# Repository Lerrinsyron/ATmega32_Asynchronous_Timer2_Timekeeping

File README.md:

ATmega32 Asynchronous Timer2 Timekeeping

CT 321 — Group 13 

Low-power real-time clock using ATmega32 Timer2 in asynchronous mode, driven by a 32.768 kHz watch crystal on TOSC1/TOSC2. The CPU sleeps between timer events; Timer2 keeps running and wakes the CPU exactly once per second.

Build
```bash
cd firmware

# Real hardware
avr-gcc -mmcu=atmega32 -DF_CPU=8000000UL -Os -I/usr/avr/include \
  -o hex/firmware.elf src/main.c
avr-objcopy -O ihex -R .eeprom hex/firmware.elf hex/firmware.hex

# SimulIDE
avr-gcc -mmcu=atmega32 -DF_CPU=8000000UL -DSIMULIDE_MODE -Os -I/usr/avr/include \
  -o hex/firmware_simulide.elf src/main.c
avr-objcopy -O ihex -R .eeprom hex/firmware_simulide.elf hex/firmware_simulide.hex
```

If `/usr/avr/include` doesn't exist on your machine, run `find /usr -name "io.h" | grep avr` to find your avr-libc path.

SimulIDE

Load hex/firmware_simulide.hex into the ATmega32. Set Freq to `8000000` and Serial Monitor baud to `9600`.

> ⚠️ Known limitation: SimulIDE cannot model the external 32.768 kHz crystal on TOSC1/TOSC2. The SIMULIDE_MODE   build uses an internal-clock CTC fallback to produce the same 1-second tick. The KiCad design remains correct for real hardware.

Common Issues

Garbage output on serial monitor baud rate mismatch. Confirm SimulIDE Serial Monitor is set to 9600, not 4800.

"SLEEP instruction not fully implemented" warning expected. SimulIDE does not model power-save sleep. Ignore it; everything else works correctly.

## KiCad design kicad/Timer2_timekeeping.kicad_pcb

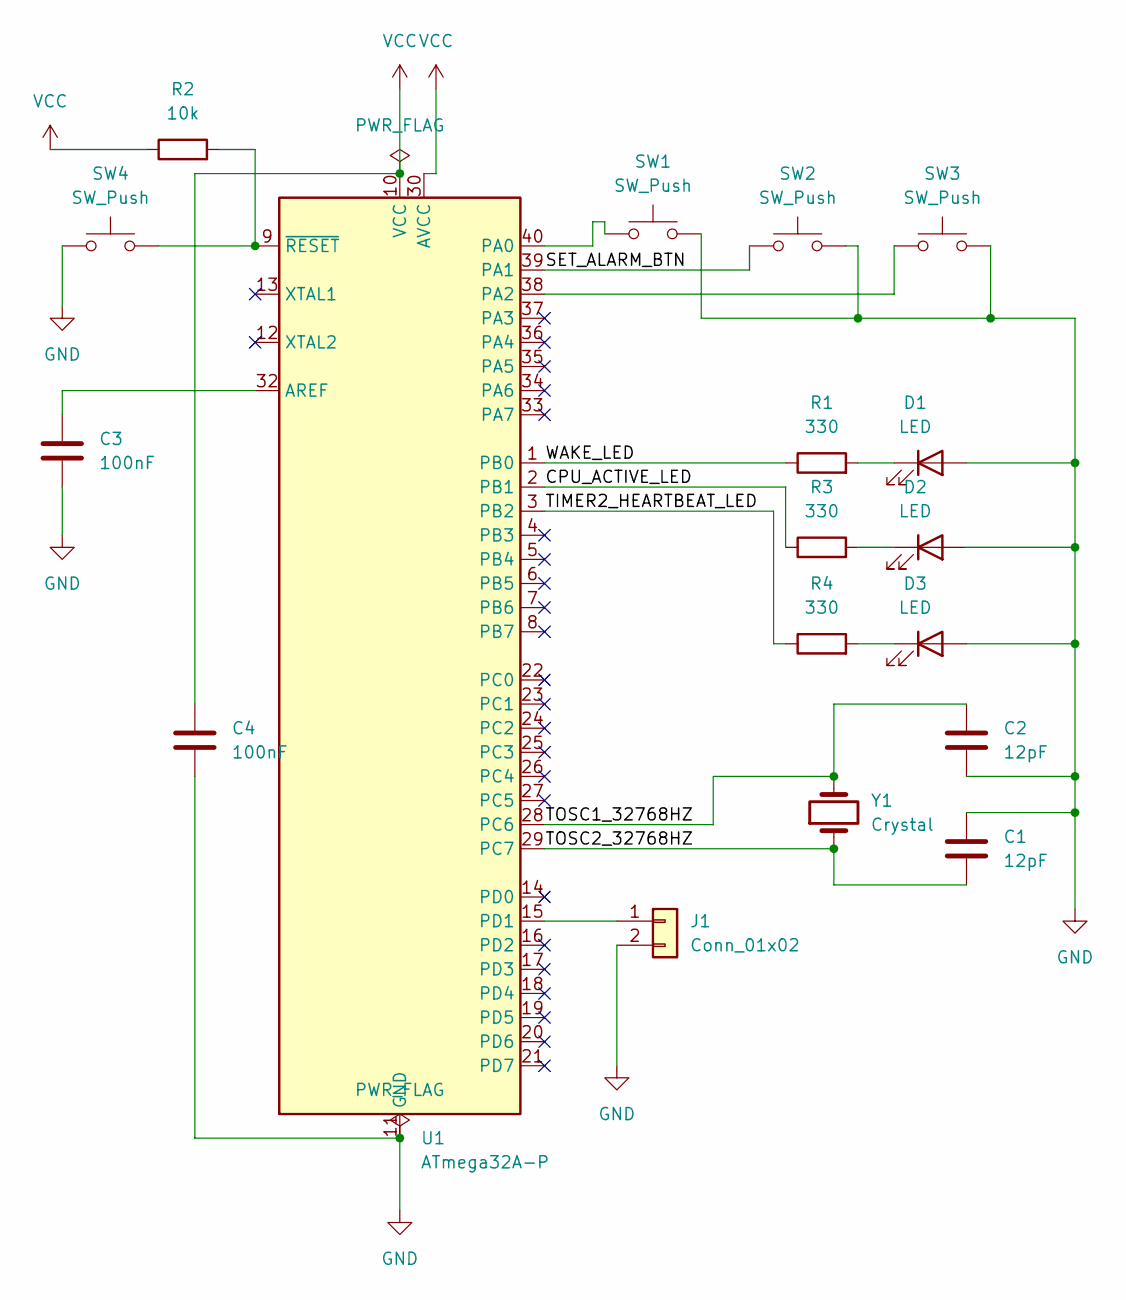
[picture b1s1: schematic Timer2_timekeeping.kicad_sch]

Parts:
C1, C2: 12pF; C_Disc_D5.0mm_W2.5mm_P5.00mm
C3, C4: 100nF; C_Disc_D5.0mm_W2.5mm_P5.00mm
D1, D2, D3: LED; LED_D5.0mm
J1: Conn_01x02; PinHeader_1x02_P2.54mm_Vertical
R1, R3, R4: 330; R_Axial_DIN0207_L6.3mm_D2.5mm_P7.62mm_Horizontal
R2: 10k; R_Axial_DIN0207_L6.3mm_D2.5mm_P7.62mm_Horizontal
SW1, SW2, SW3, SW4: SW_Push; SW_PUSH_6mm
U1: ATmega32A-P; DIP-40_W15.24mm
Y1: Crystal; Crystal_HC49-4H_Vertical

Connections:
/CPU_ACTIVE_LED: R3.1, U1.2 (PB1)
/SET_ALARM_BTN: SW2.1, U1.39 (PA1)
/TIMER2_HEARTBEAT_LED: R4.1, U1.3 (PB2)
/TOSC1_32768HZ: C2.1, U1.28 (PC6), Y1.2
/TOSC2_32768HZ: C1.2, U1.29 (PC7), Y1.1
/WAKE_LED: R1.1, U1.1 (PB0)
GND: C1.1, C2.2, C3.2, C4.1, D1.2 (A), D2.2 (A), D3.2 (A), J1.2, SW1.2, SW2.2, SW3.2, SW4.1, U1.11 (GND), U1.31 (GND)
unnamed: D1.1 (K), R1.2
unnamed: D2.1 (K), R3.2
unnamed: D3.1 (K), R4.2
unnamed: J1.1, U1.15 (PD1)
unnamed: C3.1, U1.32 (AREF)
unnamed: SW1.1, U1.40 (PA0)
unnamed: SW3.1, U1.38 (PA2)
unnamed: R2.2, SW4.2, U1.9 (~RESET)
VCC: C4.2, R2.1, U1.10 (VCC), U1.30 (AVCC)

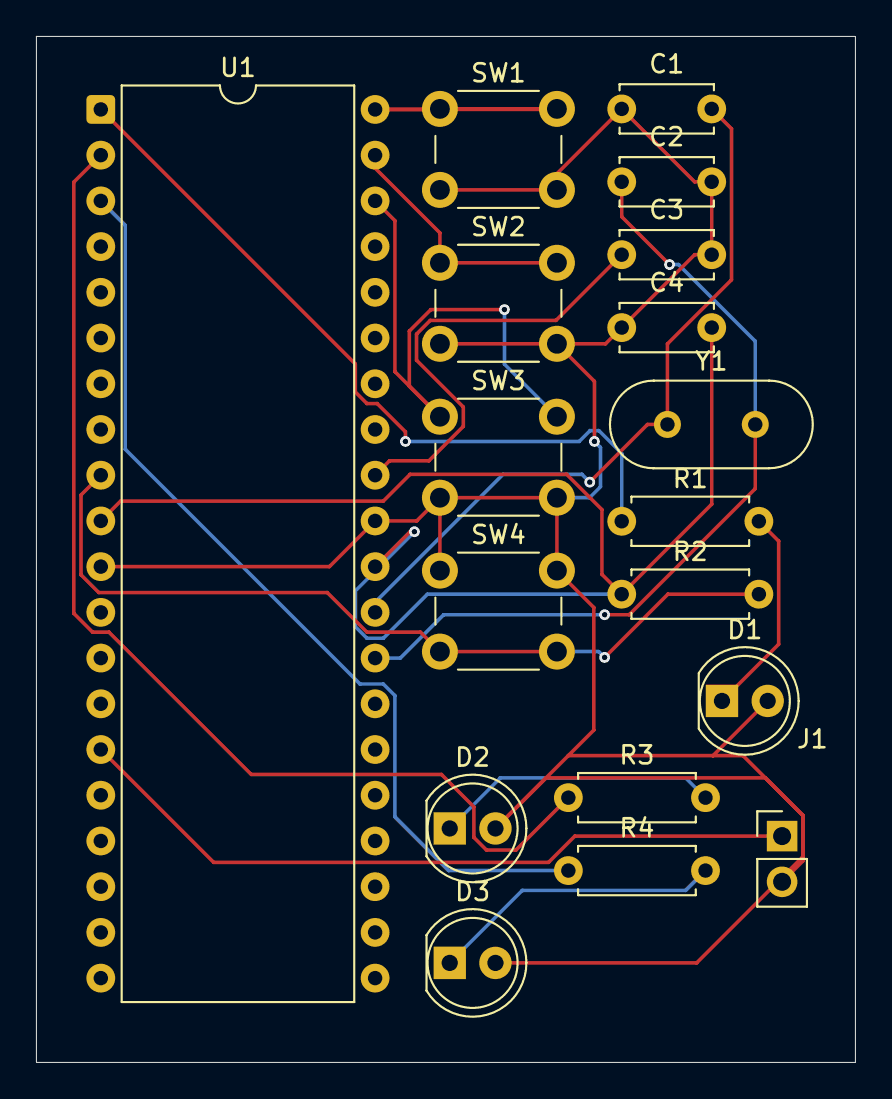
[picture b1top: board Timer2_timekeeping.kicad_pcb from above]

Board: 2 copper layers, 45.5 x 57.0 mm, 18 parts (0 on the bottom side), 16 nets.

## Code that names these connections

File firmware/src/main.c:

#define F_CPU 8000000UL

#include <avr/interrupt.h>
#include <avr/io.h>
#include <avr/sleep.h>
#include <stdbool.h>
#include <stdio.h>
#include <string.h>
#include <util/delay.h>

// configs
#define WAKE_LED_PIN PB0
#define BUZZER_PIN PB1
#define BTN_RESET PA0
#define BTN_SET_ALARM PA1
#define BTN_INCREMENT PA2

#define ALARM_BUZZ_DURATION 3

#define WAKEUP_INTERVAL 10

#define BAUD 9600
#define UBRR_VALUE ((F_CPU / (16UL * BAUD)) - 1) // = 51 at 8 MHz 

volatile uint8_t g_seconds = 0;
volatile uint8_t g_minutes = 0;
volatile uint8_t g_hours = 0;

volatile uint8_t g_alarm_seconds = 0;
volatile uint8_t g_alarm_minutes = 0;
volatile uint8_t g_alarm_hours = 0;

volatile bool g_time_updated = false; 
volatile bool g_alarm_ringing = false;
volatile uint8_t g_buzz_countdown = 0; 

#ifdef SIMULIDE_MODE
volatile uint8_t g_tick_count = 0;
#define TICKS_PER_SECOND 100 
#endif

typedef enum
{
  MODE_CLOCK,       
  MODE_SET_ALARM_H, 
  MODE_SET_ALARM_M, 
  MODE_SET_ALARM_S  
} AppMode;

volatile AppMode g_mode = MODE_CLOCK;


static void usart_init(void)
{
  UBRRH = (uint8_t)(UBRR_VALUE >> 8);
  UBRRL = (uint8_t)(UBRR_VALUE);
  UCSRB = (1 << TXEN);                                
  UCSRC = (1 << URSEL) | (1 << UCSZ1) | (1 << UCSZ0); 
}

static void usart_putchar(char c)
{
  while (!(UCSRA & (1 << UDRE)))
    ;
  UDR = c;
}

static void usart_print(const char *str)
{
  while (*str)
    usart_putchar(*str++);
}

static void usart_print_time(uint8_t h, uint8_t m, uint8_t s,
                             const char *label)
{
  char buf[32];
  snprintf(buf, sizeof(buf), "%s %02u:%02u:%02u\r\n", label, h, m, s);
  usart_print(buf);
}

static void gpio_init(void)
{
  DDRB |= (1 << WAKE_LED_PIN) | (1 << BUZZER_PIN) | (1 << PB2) | (1 << PB3);
  PORTB &= ~((1 << WAKE_LED_PIN) | (1 << BUZZER_PIN) | (1 << PB2) | (1 << PB3)); 

  DDRA &= ~((1 << BTN_RESET) | (1 << BTN_SET_ALARM) | (1 << BTN_INCREMENT));
  PORTA |= (1 << BTN_RESET) | (1 << BTN_SET_ALARM) | (1 << BTN_INCREMENT);
}

static void timer2_init(void)
{
#ifndef SIMULIDE_MODE
  //Async clock source
  ASSR |= (1 << AS2);

  TCNT2 = 0;

  TCCR2 = (1 << CS22) | (1 << CS20);

  while (ASSR & ((1 << TCN2UB) | (1 << OCR2UB) | (1 << TCR2UB)))
    ;
  TIMSK |= (1 << TOIE2);

#else
  TCCR2 = (1 << WGM21)                               
          | (1 << CS22) | (1 << CS21) | (1 << CS20); 
  OCR2 = 77;                                         
  TIMSK |= (1 << OCIE2);                            
#endif
}

#ifndef SIMULIDE_MODE

ISR(TIMER2_OVF_vect)
{
  g_seconds++;
  if (g_seconds >= 60)
  {
    g_seconds = 0;
    g_minutes++;
  }
  if (g_minutes >= 60)
  {
    g_minutes = 0;
    g_hours++;
  }
  if (g_hours >= 24)
  {
    g_hours = 0;
  }

  if (g_seconds % WAKEUP_INTERVAL == 0)
    PORTB ^= (1 << WAKE_LED_PIN);

  if (!g_alarm_ringing && g_hours == g_alarm_hours &&
      g_minutes == g_alarm_minutes && g_seconds == g_alarm_seconds)
  {
    g_alarm_ringing = true;
    g_buzz_countdown = ALARM_BUZZ_DURATION;
    PORTB |= (1 << BUZZER_PIN);
  }


  if (g_alarm_ringing)
  {
    if (g_buzz_countdown > 0)
    {
      g_buzz_countdown--;
    }
    else
    {
      g_alarm_ringing = false;
      PORTB &= ~(1 << BUZZER_PIN);
    }
  }

  PORTB ^= (1 << PB3);
  g_time_updated = true;
}

#else 
ISR(TIMER2_COMP_vect)
{
  g_tick_count++;
  if (g_tick_count < TICKS_PER_SECOND)
    return; 
  g_tick_count = 0;

  
  g_seconds++;
  if (g_seconds >= 60)
  {
    g_seconds = 0;
    g_minutes++;
  }
  if (g_minutes >= 60)
  {
    g_minutes = 0;
    g_hours++;
  }
  if (g_hours >= 24)
  {
    g_hours = 0;
  }

  if (g_seconds % WAKEUP_INTERVAL == 0)
    PORTB ^= (1 << WAKE_LED_PIN);

  if (!g_alarm_ringing && g_hours == g_alarm_hours &&
      g_minutes == g_alarm_minutes && g_seconds == g_alarm_seconds)
  {
    g_alarm_ringing = true;
    g_buzz_countdown = ALARM_BUZZ_DURATION;
    PORTB |= (1 << BUZZER_PIN);
  }

  if (g_alarm_ringing)
  {
    if (g_buzz_countdown > 0)
    {
      g_buzz_countdown--;
    }
    else
    {
      g_alarm_ringing = false;
      PORTB &= ~(1 << BUZZER_PIN);
    }
  }

  PORTB ^= (1 << PB3);
  g_time_updated = true;
}

#endif 

static bool button_pressed(uint8_t pin)
{
  if (!(PINA & (1 << pin)))
  {                           
    _delay_ms(20);            
    if (!(PINA & (1 << pin))) 
      return true;
  }
  return false;
}

static void handle_buttons(void)
{
  if (button_pressed(BTN_RESET))
  {
    cli(); 
    g_seconds = 0;
    g_minutes = 0;
    g_hours = 0;
    g_alarm_ringing = false;
    g_buzz_countdown = 0;
    PORTB &= ~((1 << WAKE_LED_PIN) | (1 << BUZZER_PIN));
    g_mode = MODE_CLOCK;
    sei();
    usart_print("TIME RESET TO 00:00:00\r\n");
    while (!(PINA & (1 << BTN_RESET)))
      ;
    _delay_ms(20);
    return;
  }

  if (button_pressed(BTN_SET_ALARM))
  {
    switch (g_mode)
    {
    case MODE_CLOCK:
      g_mode = MODE_SET_ALARM_H;
      break;
    case MODE_SET_ALARM_H:
      g_mode = MODE_SET_ALARM_M;
      break;
    case MODE_SET_ALARM_M:
      g_mode = MODE_SET_ALARM_S;
      break;
    case MODE_SET_ALARM_S:
      g_mode = MODE_CLOCK;
      break;
    }
    while (!(PINA & (1 << BTN_SET_ALARM)))
      ;
    _delay_ms(20);
  }

  if (button_pressed(BTN_INCREMENT))
  {
    switch (g_mode)
    {
    case MODE_CLOCK:
      break; 
    case MODE_SET_ALARM_H:
      g_alarm_hours = (g_alarm_hours + 1) % 24;
      break;
    case MODE_SET_ALARM_M:
      g_alarm_minutes = (g_alarm_minutes + 1) % 60;
      break;
    case MODE_SET_ALARM_S:
      g_alarm_seconds = (g_alarm_seconds + 1) % 60;
      break;
    }
    while (!(PINA & (1 << BTN_INCREMENT)))
      ;
    _delay_ms(20);
  }
}

static void update_display(void)
{
  cli();
  uint8_t h = g_hours, m = g_minutes, s = g_seconds;
  uint8_t ah = g_alarm_hours, am = g_alarm_minutes, as_ = g_alarm_seconds;
  AppMode mode = g_mode;
  g_time_updated = false;
  sei();

  usart_print_time(h, m, s, "TIME: ");

  usart_print_time(ah, am, as_, "ALRM: ");

  switch (mode)
  {
  case MODE_CLOCK:
    usart_print("MODE: LOW POWER\r\n");
    break;
  case MODE_SET_ALARM_H:
    usart_print("MODE: SET ALARM HH\r\n");
    break;
  case MODE_SET_ALARM_M:
    usart_print("MODE: SET ALARM MM\r\n");
    break;
  case MODE_SET_ALARM_S:
    usart_print("MODE: SET ALARM SS\r\n");
    break;
  }
  usart_print("---\r\n");
}

static void enter_sleep(void)
{
#ifdef SIMULIDE_MODE
  return; 
#else
  set_sleep_mode(SLEEP_MODE_PWR_SAVE);
  sleep_enable();
  sei();
  sleep_cpu();
  sleep_disable();
#endif
}

int main(void)
{
  gpio_init();
  usart_init();
  timer2_init();
  sei(); 

  usart_print("\r\n== ATmega32 Async Timer2 Timekeeping ==\r\n");
#ifdef SIMULIDE_MODE
  usart_print("(SimulIDE mode: internal clock fallback)\r\n");
#else
  usart_print("(Hardware mode: 32.768 kHz TOSC crystal)\r\n");
#endif
  usart_print("Buttons: PA0=Reset  PA1=SetAlarm  PA2=Increment\r\n");
  usart_print("---\r\n");

  update_display();

  while (1)
  {
    PORTB |= (1 << PB2);
    handle_buttons();

    if (g_time_updated)
      update_display();
    PORTB &= ~(1 << PB2);
    enter_sleep();
  }

  return 0;
}
